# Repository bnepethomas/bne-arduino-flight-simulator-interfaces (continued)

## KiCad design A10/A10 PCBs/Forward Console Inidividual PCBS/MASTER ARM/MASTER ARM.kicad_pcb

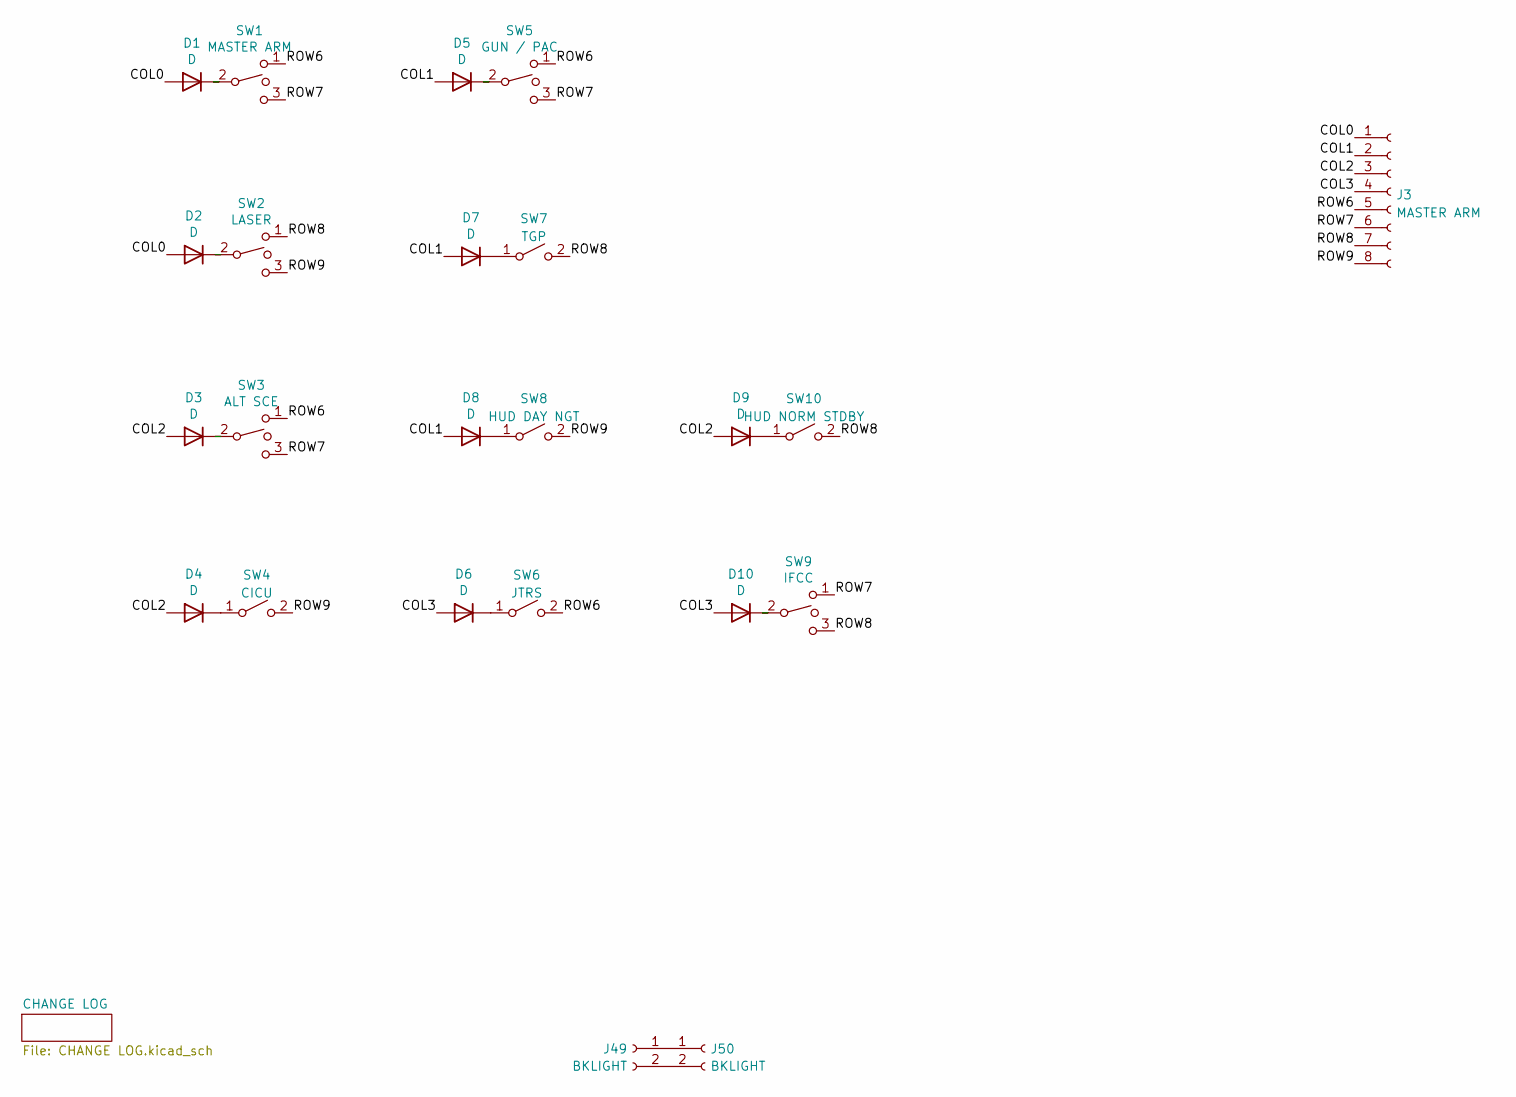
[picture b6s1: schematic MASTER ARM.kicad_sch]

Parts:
D1, D2, D3, D4, D5, D6, D7, D8, D9, D10: D; D_A-405_P2.54mm_Vertical_AnodeUp
J3: MASTER ARM; Molex_KK-254_AE-6410-08A_1x08_P2.54mm_Vertical
J49, J50: BKLIGHT; Molex_KK-254_AE-6410-02A_1x02_P2.54mm_Vertical
SW1: MASTER ARM; Molex_KK-254_AE-6410-03A_1x03_P2.54mm_Vertical
SW2: LASER; Molex_KK-254_AE-6410-03A_1x03_P2.54mm_Vertical
SW3: ALT SCE; Molex_KK-254_AE-6410-03A_1x03_P2.54mm_Vertical
SW4: CICU; Molex_KK-254_AE-6410-02A_1x02_P2.54mm_Vertical
SW5: GUN / PAC; Molex_KK-254_AE-6410-03A_1x03_P2.54mm_Vertical
SW6: JTRS; Molex_KK-254_AE-6410-02A_1x02_P2.54mm_Vertical
SW7: TGP; Molex_KK-254_AE-6410-02A_1x02_P2.54mm_Vertical
SW8: HUD DAY NGT; Molex_KK-254_AE-6410-02A_1x02_P2.54mm_Vertical
SW9: IFCC; Molex_KK-254_AE-6410-03A_1x03_P2.54mm_Vertical
SW10: HUD NORM STDBY; Molex_KK-254_AE-6410-02A_1x02_P2.54mm_Vertical

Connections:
/COL0: D1.2 (A), D2.2 (A), J3.1
/COL1: D5.2 (A), D7.2 (A), D8.2 (A), J3.2
/COL2: D3.2 (A), D4.2 (A), D9.2 (A), J3.3
/COL3: D6.2 (A), D10.2 (A), J3.4
/ROW6: J3.5, SW1.1, SW3.1, SW5.1, SW6.2 (B)
/ROW7: J3.6, SW1.3, SW3.3, SW5.3, SW9.1
/ROW8: J3.7, SW2.1, SW7.2 (B), SW9.3, SW10.2 (B)
/ROW9: J3.8, SW2.3, SW4.2 (B), SW8.2 (B)
unnamed: D1.1 (K), SW1.2
unnamed: D2.1 (K), SW2.2
unnamed: D3.1 (K), SW3.2
unnamed: D4.1 (K), SW4.1 (A)
unnamed: D5.1 (K), SW5.2
unnamed: D6.1 (K), SW6.1 (A)
unnamed: D7.1 (K), SW7.1 (A)
unnamed: D8.1 (K), SW8.1 (A)
unnamed: D9.1 (K), SW10.1 (A)
unnamed: D10.1 (K), SW9.2

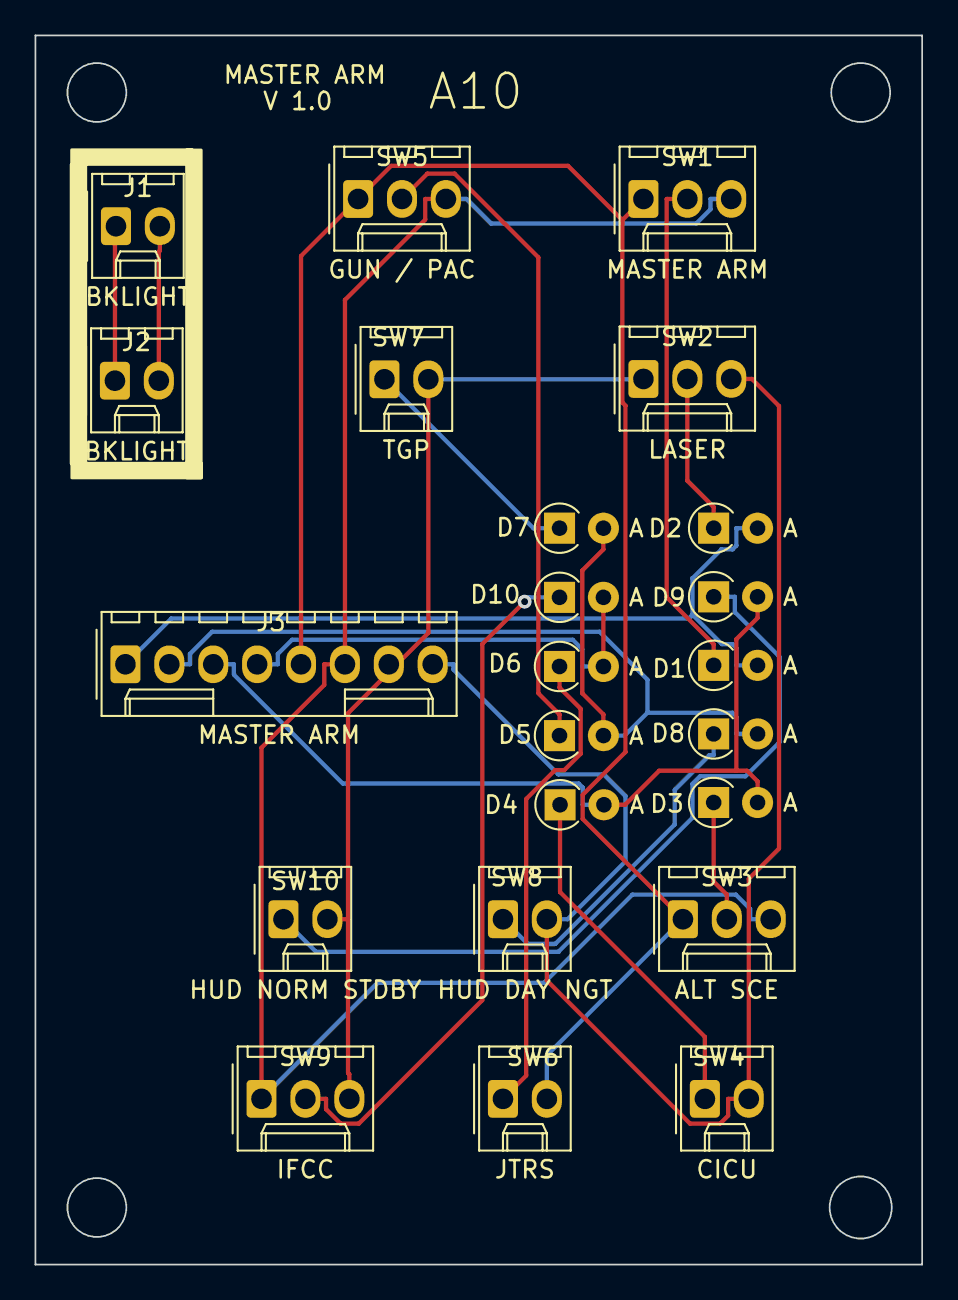
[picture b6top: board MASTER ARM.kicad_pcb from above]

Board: 2 copper layers, 51.3 x 71.1 mm, 23 parts (0 on the bottom side), 20 nets.

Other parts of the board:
J1, J2: BKLIGHT; Molex_KK-254_AE-6410-02A_1x02_P2.54mm_Vertical

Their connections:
unnamed: J1.1, J2.1
unnamed: J1.2, J2.2

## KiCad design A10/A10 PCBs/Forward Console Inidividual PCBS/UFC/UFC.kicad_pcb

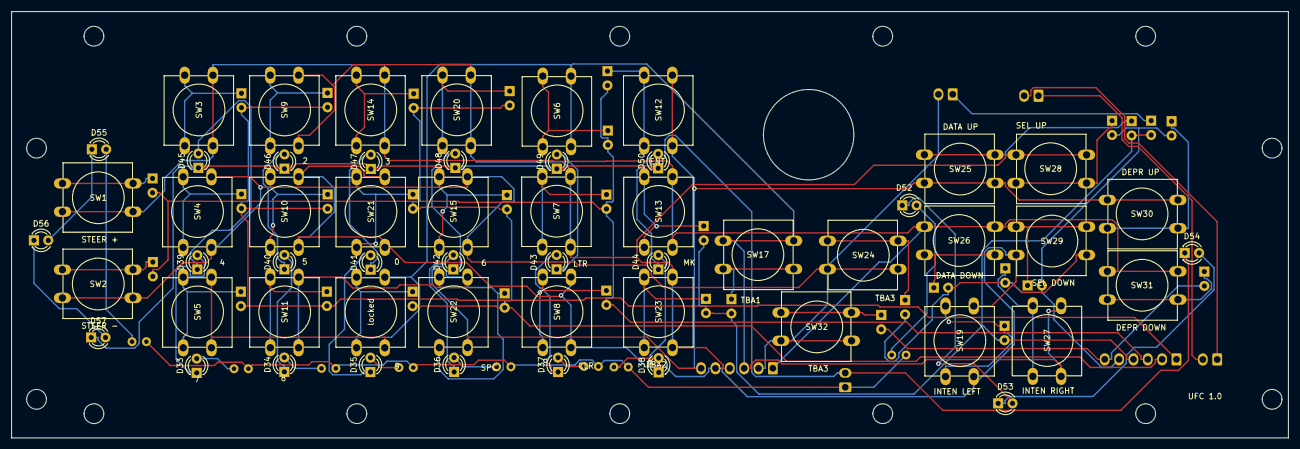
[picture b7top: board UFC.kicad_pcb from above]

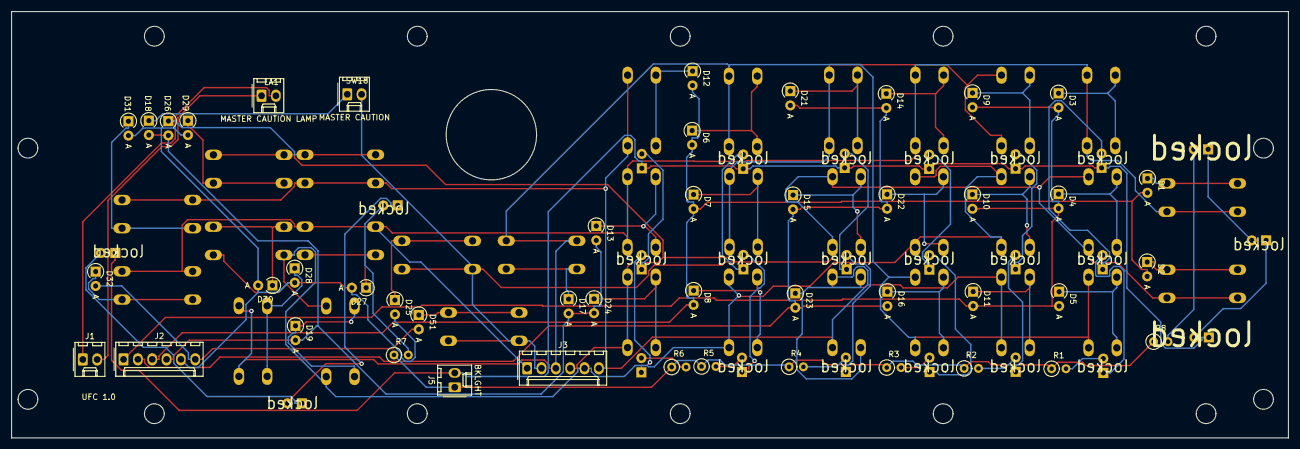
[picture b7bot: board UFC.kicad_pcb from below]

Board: 2 copper layers, 226.1 x 75.5 mm, 101 parts (46 on the bottom side), 72 nets.

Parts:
D1, D2, D3, D4, D5, D6, D7, D8, D9, D10, D11, D12, D13, D14, D15, D16, D17, D18, D19, D21, D22, D23, D24, D25, D26, D27, D28, D29, D30, D31, D32, D51: D; D_A-405_P2.54mm_Vertical_AnodeUp
D33, D34, D35, D36, D37, D38, D39, D40, D41, D42, D43, D44, D45, D46, D47, D48, D49, D50, D52, D53, D54, D55, D56, D57: LED; LED_D3.0mm_FlatTop
J1: CAUTION LAMP; Molex_KK-254_AE-6410-02A_1x02_P2.54mm_Vertical
J2: UFC COLS; Molex_KK-254_AE-6410-06A_1x06_P2.54mm_Vertical
J3: UFC ROWS; Molex_KK-254_AE-6410-06A_1x06_P2.54mm_Vertical
J5: BKLGHT; Molex_KK-254_AE-6410-02A_1x02_P2.54mm_Vertical
LA1: MASTER CAUTION LAMP; Molex_KK-254_AE-6410-02A_1x02_P2.54mm_Vertical
R1, R2, R3, R4, R5, R6, R7, R8: R_US; R_Axial_DIN0207_L6.3mm_D2.5mm_P2.54mm_Vertical
SW1: STEER +; SW_PUSH-12mm
SW2: STEER -; SW_PUSH-12mm
SW3: 1; SW_PUSH-12mm
SW4: 4; SW_PUSH-12mm
SW5: 7; SW_PUSH-12mm
SW6: FUNC; SW_PUSH-12mm
SW7: LTR; SW_PUSH-12mm
SW8: CLR; SW_PUSH-12mm
SW9: 2; SW_PUSH-12mm
SW10: 5; SW_PUSH-12mm
SW11: 8; SW_PUSH-12mm
SW12: ENT; SW_PUSH-12mm
SW13: MK; SW_PUSH-12mm
SW14: 3; SW_PUSH-12mm
SW15: 6; SW_PUSH-12mm
SW17: TBA1; SW_PUSH-12mm
SW18: MASTER CAUTION; Molex_KK-254_AE-6410-02A_1x02_P2.54mm_Vertical
SW19: INTEN LEFT; SW_PUSH-12mm
SW20: POS; SW_PUSH-12mm
SW21: 0; SW_PUSH-12mm
SW22: SPC; SW_PUSH-12mm
SW23: TBA2; SW_PUSH-12mm
SW24, SW32: TBA3; SW_PUSH-12mm
SW25: DATA UP; SW_PUSH-12mm
SW26: DATA DOWN; SW_PUSH-12mm
SW27: INTEN RIGHT; SW_PUSH-12mm
SW28: SEL UP; SW_PUSH-12mm
SW29: SEL DOWN; SW_PUSH-12mm
SW30: DEPR UP; SW_PUSH-12mm
SW31: DEPR DOWN; SW_PUSH-12mm
locked: 9; SW_PUSH-12mm

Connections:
/BACKLIGHTING/BACKLIGHT_+12V: J5.1, R1.1, R2.1, R3.1, R4.1, R5.1, R6.1, R7.1, R8.1
/BACKLIGHTING/BACKLIGHT_GND: D45.1 (K), D46.1 (K), D47.1 (K), D48.1 (K), D49.1 (K), D50.1 (K), D54.1 (K), D57.1 (K), J5.2
/CAUTION_LAMP+: J1.1, LA1.2 (+)
/CAUTION_LAMP-: J1.2, LA1.1 (-)
/COL0: D3.2 (A), D4.2 (A), D5.2 (A), D9.2 (A), D10.2 (A), D11.2 (A), J2.1
/COL1: D14.2 (A), D15.2 (A), D16.2 (A), D21.2 (A), D22.2 (A), D23.2 (A), J2.2
/COL2: D1.2 (A), D2.2 (A), D6.2 (A), D7.2 (A), D8.2 (A), D12.2 (A), J2.3
/COL3: D13.2 (A), D17.2 (A), D18.2 (A), D19.2 (A), D24.2 (A), D26.2 (A), J2.4
/COL4: D25.2 (A), D27.2 (A), D28.2 (A), D29.2 (A), D30.2 (A), D31.2 (A), J2.5
/COL5: D32.2 (A), D51.2 (A), J2.6
/ROW0: J3.1, SW1.2, SW3.2, SW13.2, SW14.2, SW26.2, SW31.2
/ROW1: J3.2, SW2.2, SW4.2, SW15.2, SW18.2, SW24.2, SW32.2
/ROW2: J3.3, SW5.2, SW6.2, SW17.2, SW27.2, locked.2
/ROW3: J3.4, SW7.2, SW9.2, SW20.2, SW23.2, SW28.2
/ROW4: J3.5, SW8.2, SW10.2, SW19.2, SW21.2, SW29.2
/ROW5: J3.6, SW11.2, SW12.2, SW22.2, SW25.2, SW30.2
unnamed: D1.1 (K), SW1.1
unnamed: D2.1 (K), SW2.1
unnamed: D3.1 (K), SW3.1
unnamed: D4.1 (K), SW4.1
unnamed: D5.1 (K), SW5.1
unnamed: D6.1 (K), SW6.1
unnamed: D7.1 (K), SW7.1
unnamed: D8.1 (K), SW8.1
unnamed: D9.1 (K), SW9.1
unnamed: D10.1 (K), SW10.1
unnamed: D11.1 (K), SW11.1
unnamed: D12.1 (K), SW12.1
unnamed: D13.1 (K), SW13.1
unnamed: D14.1 (K), SW14.1
unnamed: D15.1 (K), SW15.1
unnamed: D16.1 (K), locked.1
unnamed: D17.1 (K), SW17.1
unnamed: D18.1 (K), SW18.1
unnamed: D19.1 (K), SW19.1
unnamed: D21.1 (K), SW20.1
unnamed: D22.1 (K), SW21.1
unnamed: D23.1 (K), SW22.1
unnamed: D24.1 (K), SW23.1
unnamed: D25.1 (K), SW24.1
unnamed: D26.1 (K), SW25.1
unnamed: D27.1 (K), SW26.1
unnamed: D28.1 (K), SW27.1
unnamed: D29.1 (K), SW28.1
unnamed: D30.1 (K), SW29.1
unnamed: D31.1 (K), SW30.1
unnamed: D32.1 (K), SW31.1
unnamed: D33.2 (A), R1.2
unnamed: D33.1 (K), D39.2 (A)
unnamed: D34.2 (A), R2.2
unnamed: D34.1 (K), D40.2 (A)
unnamed: D35.2 (A), R3.2
unnamed: D35.1 (K), D41.2 (A)
unnamed: D36.2 (A), R4.2
unnamed: D36.1 (K), D42.2 (A)
unnamed: D37.2 (A), R5.2
unnamed: D37.1 (K), D43.2 (A)
unnamed: D38.2 (A), R6.2
unnamed: D38.1 (K), D44.2 (A)
unnamed: D39.1 (K), D45.2 (A)
unnamed: D40.1 (K), D46.2 (A)
unnamed: D41.1 (K), D47.2 (A)
unnamed: D42.1 (K), D48.2 (A)
unnamed: D43.1 (K), D49.2 (A)
unnamed: D44.1 (K), D50.2 (A)
unnamed: D51.1 (K), SW32.1
unnamed: D52.2 (A), R7.2
unnamed: D52.1 (K), D53.2 (A)
unnamed: D53.1 (K), D54.2 (A)
unnamed: D55.2 (A), R8.2
unnamed: D55.1 (K), D56.2 (A)
unnamed: D56.1 (K), D57.2 (A)

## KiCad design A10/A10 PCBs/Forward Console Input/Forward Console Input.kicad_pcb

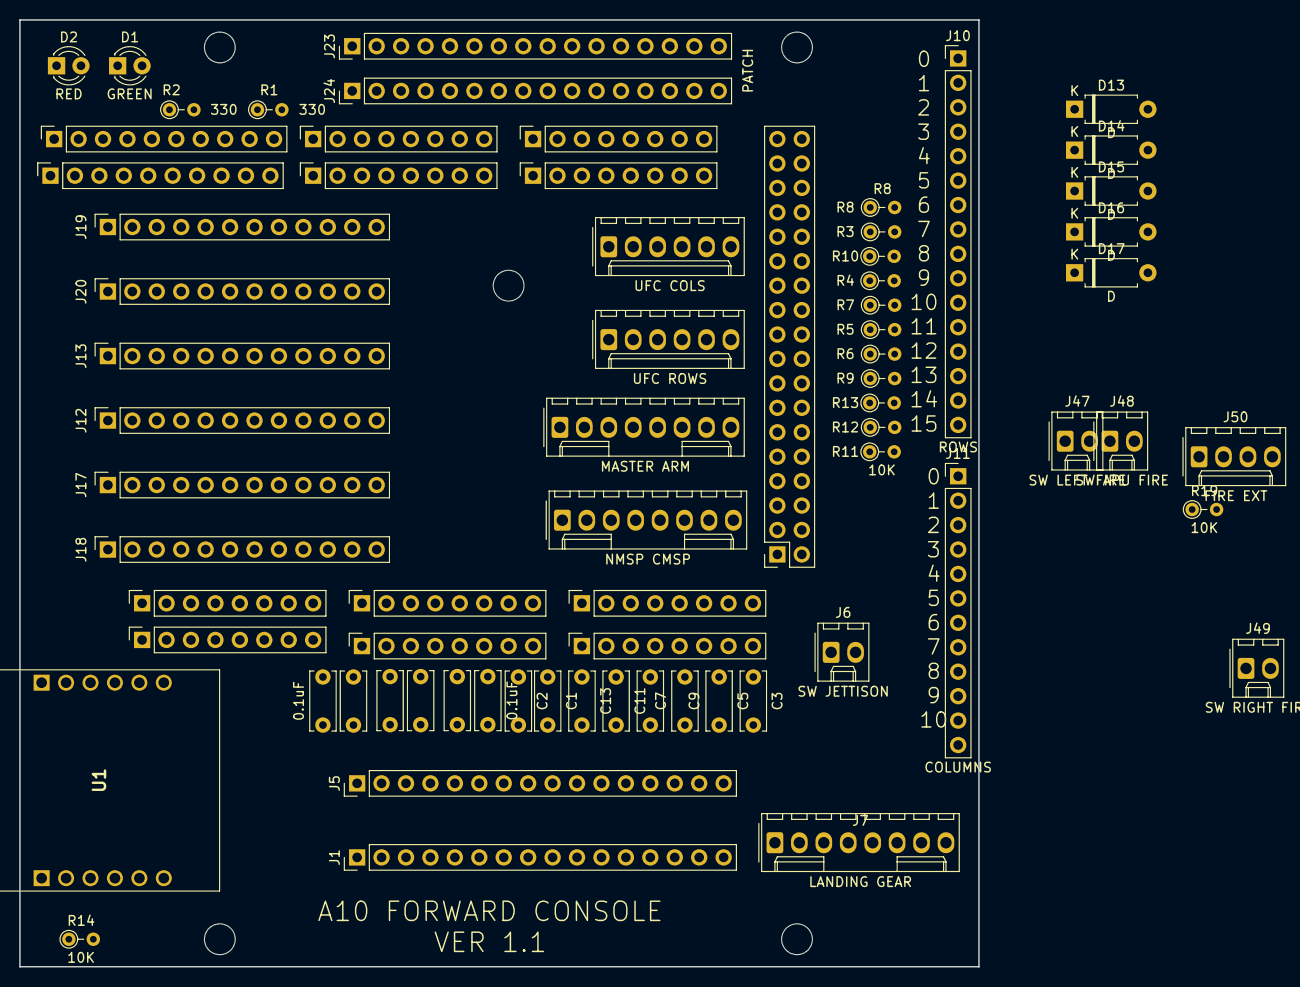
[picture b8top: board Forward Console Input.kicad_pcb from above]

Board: 2 copper layers, 99.7 x 98.4 mm, 77 parts (0 on the bottom side), 153 nets, no tracks yet.

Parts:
C1, C2, C3, C4, C5, C6, C7, C8, C9, C10, C11, C12, C13, C14: 0.1uF; C_Disc_D6.0mm_W2.5mm_P5.00mm
D1: GREEN; LED_D3.0mm
D2: RED; LED_D3.0mm
D13, D14, D15, D16, D17: D; D_A-405_P7.62mm_Horizontal
H1, H2, H3, H4: MountingHole; MountingHole_3.2mm
J1, J5, J23, J24: PATCH; PinHeader_1x16_P2.54mm_Vertical
J3: UFC COLS; Molex_KK-254_AE-6410-06A_1x06_P2.54mm_Vertical
J4: UFC ROWS; Molex_KK-254_AE-6410-06A_1x06_P2.54mm_Vertical
J6: SW JETTISON; Molex_KK-254_AE-6410-02A_1x02_P2.54mm_Vertical
J7: LANDING GEAR; Molex_KK-254_AE-6410-08A_1x08_P2.54mm_Vertical
J8: MASTER ARM; Molex_KK-254_AE-6410-08A_1x08_P2.54mm_Vertical
J9: NMSP CMSP; Molex_KK-254_AE-6410-08A_1x08_P2.54mm_Vertical
J10: ROWS; PinHeader_1x16_P2.54mm_Vertical
J11: COLUMNS; PinHeader_1x12_P2.54mm_Vertical
J12, J13, J17, J18, J19, J20: PATCH; PinSocket_1x12_P2.54mm_Vertical
J14, J30: PWM; PinSocket_1x10_P2.54mm_Vertical
J15, J31: PWM; PinSocket_1x08_P2.54mm_Vertical
J16, J32: Communication; PinSocket_1x08_P2.54mm_Vertical
J21, J22, J27, J28: Analog; PinSocket_1x08_P2.54mm_Vertical
J25, J26: Power; PinSocket_1x08_P2.54mm_Vertical
J29: Digital; PinSocket_2x18_P2.54mm_Vertical
J47: SW LEFT FIRE; Molex_KK-254_AE-6410-02A_1x02_P2.54mm_Vertical
J48: SW APU FIRE; Molex_KK-254_AE-6410-02A_1x02_P2.54mm_Vertical
J49: SW RIGHT FIRE; Molex_KK-254_AE-6410-02A_1x02_P2.54mm_Vertical
J50: FIRE EXT; Molex_KK-254_AE-6410-04A_1x04_P2.54mm_Vertical
MH1: MountingHole_3.2mm
R1, R2: 330; R_Axial_DIN0204_L3.6mm_D1.6mm_P2.54mm_Vertical
R3, R4, R5, R6, R7, R8, R9, R10, R11, R12, R13, R14, R19: 10K; R_Axial_DIN0204_L3.6mm_D1.6mm_P2.54mm_Vertical
U1: USR-ES1; USRES1

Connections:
+3V3: J25.4, J26.4, R14.1, U1.B2 (3V3_1), U1.B3 (3V3_2)
+5V: J25.5, J26.5, J29.35, J29.36, R3.1, R4.1, R5.1, R6.1, R7.1, R8.1, R9.1, R10.1, R11.1, R12.1, R13.1, R19.1
/22: J4.1, J10.1
/23: J4.2, J10.2, J29.34
/24: J4.3, J10.3
/25: J4.4, J10.4, J29.32
/26: J4.5, J10.5, J29.29
/27: J4.6, J10.6, J29.30
/28: J8.5, J9.3, J10.7
/29: J8.6, J9.4, J10.8, J29.28
/30: J8.7, J9.5, J10.9, J29.25
/31: J8.8, J9.6, J10.10, J29.26
/32: J7.3, J9.7, J10.11, J29.23, J47.2, J50.2
/33: J7.4, J9.8, J10.12, J29.24, J48.2, J50.4
/34: J7.5, J10.13, J29.21, J49.2
/35: J6.2, J7.6, J10.14, J29.22
/36: J7.7, J10.15, J29.19
/37: J7.8, J10.16, J29.20
/38: J3.1, J7.1, J8.1, J11.1, J29.17, R3.2
/39: J3.2, J7.2, J8.2, J11.2, J29.18, R4.2
/40: D13.2 (A), D14.2 (A), D15.2 (A), D16.2 (A), J3.3, J8.3, J11.3, J29.15, R5.2
/41: D17.2 (A), J3.4, J8.4, J11.4, J29.16, R6.2
/42: J3.5, J9.1, J11.5, R7.2
/43: J3.6, J9.2, J11.6, J29.14, R8.2
/47: J11.10, J29.10, R12.2
/48: J11.11, J29.7, R13.2
/49: J11.12, J29.8, R19.2
/*2: J15.6, J31.6
/*3: J15.5, J31.5
/*4: J15.4, J31.4
/*5: J15.3, J31.3
/*6: J15.2, J31.2
/*7: J15.1, J31.1
/*8: J14.10, J30.10
/*9: J14.9, J30.9
/*11: J14.7, J30.7
/*12: J14.6, J30.6, R2.1
/*13: J14.5, J30.5, R1.1
/*44: J11.7, R9.2
/*45: J11.8, J29.12, R10.2
/*46: J11.9, J29.9, R11.2
/A0: C14.1, J21.1, J27.1
/A1: C12.1, J21.2, J27.2
/A2: C10.1, J21.3, J27.3
/A3: C8.1, J21.4, J27.4
/A4: C6.1, J21.5, J27.5
/A5: C4.1, J21.6, J27.6
/A6: C2.1, J21.7, J27.7
/A7: C1.1, J21.8, J27.8
/A8: C13.1, J22.1, J28.1
/A9: C11.1, J22.2, J28.2
/A10: C9.1, J22.3, J28.3
/A11: C7.1, J22.4, J28.4
/A12: C5.1, J22.5, J28.5
/A13: C3.1, J22.6, J28.6
/A14: J22.7, J28.7
/A15: J22.8, J28.8
/AREF: J14.3, J30.3
/IOREF: J25.2, J26.2
/RX0/0: J15.8, J31.8
/RX1/19: J16.6, J32.6
/RX2/17: J16.4, J32.4
/RX3/15: J16.2, J32.2
/SCL/21: J14.1, J16.8, J30.1, J32.8
/SDA/20: J14.2, J16.7, J30.2, J32.7
/TX0/1: J15.7, J31.7
/TX1/18: J16.5, J32.5
/TX2/16: J16.3, J32.3
/TX3/14: J16.1, J32.1
/~RESET: J25.3, J26.3
ES1_RST: J29.4, U1.B5 (RST)
GND: C1.2, C2.2, C3.2, C4.2, C5.2, C6.2, C7.2, C8.2, C9.2, C10.2, C11.2, C12.2, C13.2, C14.2, D1.1 (K), D2.1 (K), J14.4, J25.6, J25.7, J26.6, J26.7, J29.1, J29.2, J30.4, U1.A1 (GND_1), U1.A2 (GND_2), U1.B1 (GND_3)
MISO: J29.5, U1.B6 (MISO)
MOSI: J29.6, U1.A3 (MOSI)
unnamed: D1.2 (A), R1.2
unnamed: D2.2 (A), R2.2
unnamed: D13.1 (K), J49.1
unnamed: D14.1 (K), J48.1
unnamed: D15.1 (K), J47.1
unnamed: D16.1 (K), J6.1
unnamed: D17.1 (K), J50.1, J50.3
unnamed: J1.1, J5.1
unnamed: J1.2, J5.2
unnamed: J1.3, J5.3
unnamed: J1.4, J5.4
unnamed: J1.5, J5.5
unnamed: J1.6, J5.6
unnamed: J1.7, J5.7
unnamed: J1.8, J5.8
unnamed: J1.9, J5.9
unnamed: J1.10, J5.10
unnamed: J1.11, J5.11
unnamed: J1.12, J5.12
unnamed: J1.13, J5.13
unnamed: J1.14, J5.14
unnamed: J1.15, J5.15
unnamed: J1.16, J5.16
unnamed: J12.1, J13.1
unnamed: J12.2, J13.2
unnamed: J12.3, J13.3
unnamed: J12.4, J13.4
unnamed: J12.5, J13.5
unnamed: J12.6, J13.6
unnamed: J12.7, J13.7
unnamed: J12.8, J13.8
unnamed: J12.9, J13.9
unnamed: J12.10, J13.10
unnamed: J12.11, J13.11
unnamed: J12.12, J13.12
unnamed: J17.1, J18.1
unnamed: J17.2, J18.2
unnamed: J17.3, J18.3
unnamed: J17.4, J18.4
unnamed: J17.5, J18.5
unnamed: J17.6, J18.6
unnamed: J17.7, J18.7
unnamed: J17.8, J18.8
unnamed: J17.9, J18.9
unnamed: J17.10, J18.10
unnamed: J17.11, J18.11
unnamed: J17.12, J18.12
unnamed: J19.1, J20.1
unnamed: J19.2, J20.2
unnamed: J19.3, J20.3
unnamed: J19.4, J20.4
unnamed: J19.5, J20.5
unnamed: J19.6, J20.6
unnamed: J19.7, J20.7
unnamed: J19.8, J20.8
unnamed: J19.9, J20.9
unnamed: J19.10, J20.10
unnamed: J19.11, J20.11
unnamed: J19.12, J20.12
unnamed: J23.1, J24.1
unnamed: J23.2, J24.2
unnamed: J23.3, J24.3
unnamed: J23.4, J24.4
unnamed: J23.5, J24.5
unnamed: J23.6, J24.6
unnamed: J23.7, J24.7
unnamed: J23.8, J24.8
unnamed: J23.9, J24.9
unnamed: J23.10, J24.10
unnamed: J23.11, J24.11
unnamed: J23.12, J24.12
unnamed: J23.13, J24.13
unnamed: J23.14, J24.14
unnamed: J23.15, J24.15
unnamed: J23.16, J24.16
unnamed: R14.2, U1.A6 (INT)
SCLK: J29.3, U1.A4 (SCLK)
SS: J14.8, J30.8, U1.A5 (CS)
VCC: J25.8, J26.8
